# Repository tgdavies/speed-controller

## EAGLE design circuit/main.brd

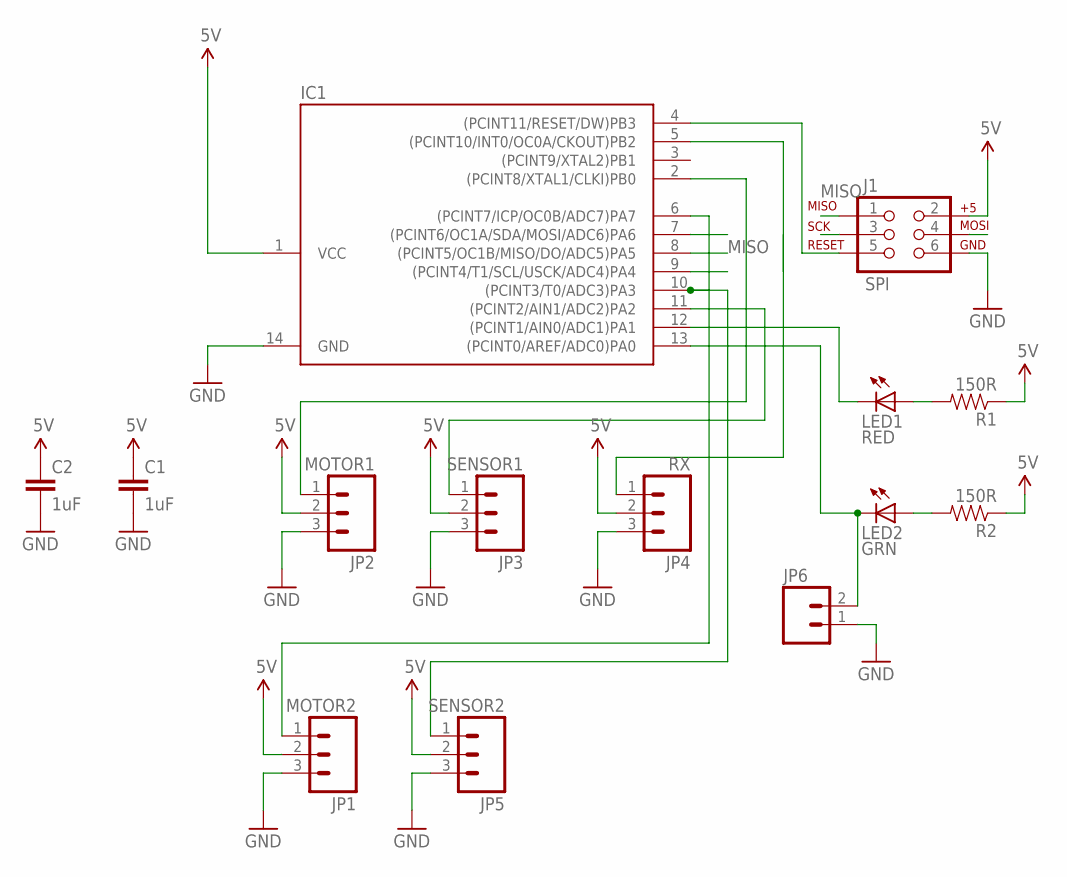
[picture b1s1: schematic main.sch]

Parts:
C1, C2: 1uF; 0805
IC1: ATTINY24/44/84-SSU; SOIC14
J1: SPI; 2X3_LOCK
JP1: MOTOR2; 1X03_LOCK
JP2: MOTOR1; 1X03_LOCK
JP3: SENSOR1; 1X03_LOCK
JP4: RX; 1X03_LOCK
JP5: SENSOR2; 1X03_LOCK
JP6: M02LOCK; 1X02_LOCK
LED1: RED; LED3MM
LED2: GRN; LED3MM
R1, R2: 150R; 0805

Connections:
5V: C1.1, C2.1, IC1.1 (VCC), J1.2, JP1.2, JP2.2, JP3.2, JP4.2, JP5.2, R1.1, R2.1
GND: C1.2, C2.2, IC1.14 (GND), J1.6, JP1.3, JP2.3, JP3.3, JP4.3, JP5.3, JP6.1
MISO: IC1.8 ((PCINT5/OC1B/MISO/DO/ADC5)PA5), J1.1
MOSI: IC1.7 ((PCINT6/OC1A/SDA/MOSI/ADC6)PA6), J1.4
unnamed: IC1.6 ((PCINT7/ICP/OC0B/ADC7)PA7), JP1.1
unnamed: IC1.5 ((PCINT10/INT0/OC0A/CKOUT)PB2), JP4.1
unnamed: IC1.10 ((PCINT3/T0/ADC3)PA3), JP5.1
unnamed: IC1.2 ((PCINT8/XTAL1/CLKI)PB0), JP2.1
unnamed: IC1.4 ((PCINT11/RESET/DW)PB3), J1.5
unnamed: IC1.12 ((PCINT1/AIN0/ADC1)PA1), LED1.K (C)
unnamed: LED1.A, R1.2
unnamed: IC1.13 ((PCINT0/AREF/ADC0)PA0), JP6.2, LED2.K (C)
unnamed: LED2.A, R2.2
unnamed: IC1.11 ((PCINT2/AIN1/ADC2)PA2), JP3.1
SCK: IC1.9 ((PCINT4/T1/SCL/USCK/ADC4)PA4), J1.3

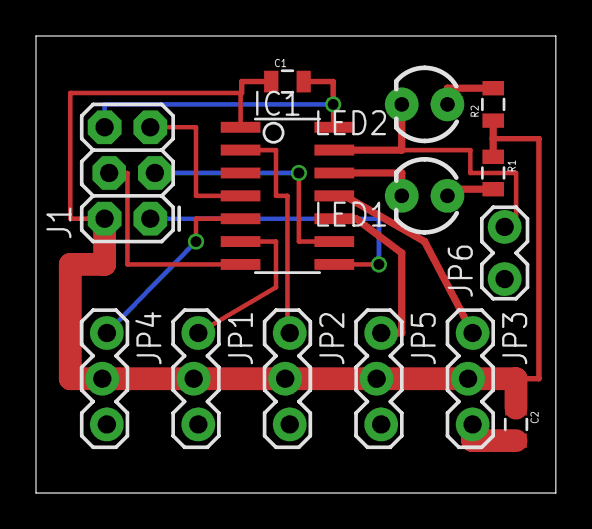
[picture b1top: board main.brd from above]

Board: 2 copper layers, 28.9 x 25.4 mm, 14 parts (0 on the bottom side), 15 nets.

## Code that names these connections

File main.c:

#include <avr/io.h>
#include <util/delay.h>
#include <avr/interrupt.h>
#include <stdint.h>
#include "avrutils.h"
#include "brushlesssensor.h"
#include "motor.h"
#include "pid.h"

#define RX_DD	(DDB2)
#define RX_P	(PB2) // Must be INT0 pin
#define MOTOR_DD (DDB0)
#define MOTOR2_DD (DDA7)
#define MOTOR_P (PB0)
#define MOTOR2_P (PA7)
#define SENSOR_DD (DDA2)
#define SENSOR2_DD (DDA3)
#define SENSOR_P (PA2)
#define SENSOR2_P (PA3) // does that work?
#define LED1_DD (DDA1)
#define LED1_P (PA1)
#define LED2_DD (DDA0)
#define LED2_P (PA0)

#define ISC0_RISE (0x03)
#define ISC0_FALL (0x02)

#define UART_SOFT_DDR DDRB 
#define UART_SOFT_PORT PORTB 
#define UART_SOFT_PIN PB1
#define UART_SOFT_BAUD (4800)

#define UART_SOFT_DELAY_US (int)(1000000.0/((float) UART_SOFT_BAUD)+0.5) 


#define softUartInit()   UART_SOFT_DDR |= (1<<UART_SOFT_PIN); \
                  UART_SOFT_PORT |= (1<<UART_SOFT_PIN)

#define DEBUG_CHARS_SIZE 9

#define readCNT1(X)         X = TCNT1L; \
        					X += TCNT1H << 8;

/*                  
char debugChars[DEBUG_CHARS_SIZE];
uint8_t sendDebug = 0;

void softUartSendChar(char txData) { 
     UART_SOFT_PORT &= ~(1<<UART_SOFT_PIN); 
     _delay_us(UART_SOFT_DELAY_US); 
   for (char i=0; i<8; i++) 
     { 
       if( txData & 1 ) 
            UART_SOFT_PORT |= (1<<UART_SOFT_PIN); 
       else 
            UART_SOFT_PORT &= ~(1<<UART_SOFT_PIN); 
       txData >>= 1; 
      _delay_us(UART_SOFT_DELAY_US); 
    } 
   UART_SOFT_PORT |= (1<<UART_SOFT_PIN); 
   _delay_us(UART_SOFT_DELAY_US); 
}

char hexDigit(int n) {
        if (n < 0xA) {
                return '0' + n;
        } else {
                return 'A' - 0xA + n;
        }
}

void clearDebugChars() {
        for (int i = 0; i < DEBUG_CHARS_SIZE; ++i) {
                debugChars[i] = 0;
        }
}

uint8_t debugIndex(uint8_t sizeNeeded) {
        uint8_t i = 0;
        while (i < DEBUG_CHARS_SIZE && debugChars[i] != 0)
                ++i;
        if (DEBUG_CHARS_SIZE - i >= sizeNeeded) {
                sendDebug = 1;
                return i;
        } else {
                return 0xff;
        }
}

void log8(uint8_t n) {
        uint8_t i = debugIndex(2);
        if (i != 0xff) {
                debugChars[i++] = hexDigit(n >> 4);
                debugChars[i] = hexDigit(n & 0x0F);
        }
}

void log16(uint16_t n) {
        uint8_t i = debugIndex(4);
        if (i != 0xff) {
                log8(n >> 8);
                log8(n & 0xFF);
        }
}

void logSep() {
        uint8_t i = debugIndex(1);
        if (i != 0xff) {
                debugChars[i] = ',';
        }
}

void logCRNL() {
        uint8_t i = debugIndex(2);
        if (i != 0xff) {
                debugChars[i++] = '\r';
                debugChars[i] = '\n';
        }
}


void softUartSendString (char *txData) 
{ 
   while(*txData != '\0') softUartSendChar(*txData++); 
}

void debugOn() {
    //PORTB |= (1 << PB4);
}

void debugOff() {
    //PORTB &= ~(1 << PB4);
}

void debugToggle() {
    //PORTB ^= (1 << PB4);
}*/


#define MAX_RPS INT16_C(50)

#define RX_COUNTS_PER_MS	125
#define RX_COUNT_STOP		62
#define RX_COUNT_DEAD_BAND	5

// controller input value after confining to 0..MAX_SPEED
volatile int16_t speed = 0;

// time to drive the motor in multiples of 4us
//volatile uint8_t drive = STOP_SPEED;

// really revs per second / 10
//volatile uint16_t actual_revs_per_second = 0;
volatile uint16_t desired_revs_per_second = 0;

#define AHEAD 1
#define ASTERN 2
volatile uint8_t desired_direction = 0;

#define BIT_DELAY_US(d,n) if (d & n) { _delay_us(n); }

void delay_us(uint16_t delay) {
    BIT_DELAY_US(delay, 0x200);
    BIT_DELAY_US(delay, 0x100);
    BIT_DELAY_US(delay, 0x80);
    BIT_DELAY_US(delay, 0x40);
    BIT_DELAY_US(delay, 0x20);
    BIT_DELAY_US(delay, 0x10);
    BIT_DELAY_US(delay, 0x08);
    BIT_DELAY_US(delay, 0x04);
    BIT_DELAY_US(delay, 0x02);
    BIT_DELAY_US(delay, 0x01);
}



//uint16_t debug_error = 0;
volatile uint16_t rx_signal_start_time = 0;
volatile uint16_t rx_signal_end_time = 0;

ISR(INT0_vect) {
    if (MCUCR != ISC0_RISE) {

        MCUCR = ISC0_RISE;
        rx_signal_end_time = TCNT1L;
        rx_signal_end_time += TCNT1H << 8;


        /*clearDebugChars();
        //log8(speed);
        //logSep();
        log8(desired_revs_per_second & 0xff);
        logSep();
        log16(actual_revs_per_second);
        //log8(v & 0xff);
        //logSep();
        //log8(error & 0xff);
        logCRNL();
                if (desired_revs_per_second == 0) {
                }*/
    } else {
        MCUCR = ISC0_FALL;
        rx_signal_start_time = TCNT1L;
        rx_signal_start_time += TCNT1H << 8;
        rx_signal_end_time = 0;
    }
}

void process_rx_result() {
    if (rx_signal_start_time != 0 && rx_signal_end_time != 0) {
        uint16_t v = timer_diff(rx_signal_start_time, rx_signal_end_time);
        if (v > RX_COUNTS_PER_MS * 3) { // invalid
            speed = RX_COUNT_STOP;
        } else if (v > RX_COUNTS_PER_MS * 2) {
            speed = RX_COUNTS_PER_MS;
        } else if (v < RX_COUNTS_PER_MS) {
            speed = 0;
        } else {
            speed = v - RX_COUNTS_PER_MS;
        }

        if (speed > RX_COUNT_STOP - RX_COUNT_DEAD_BAND && speed < RX_COUNT_STOP + RX_COUNT_DEAD_BAND) {
            speed = RX_COUNT_STOP;
            desired_revs_per_second = 0;
            desired_direction = 0;
            //debugOn();

        } else if (speed >= RX_COUNT_STOP + RX_COUNT_DEAD_BAND) {
            desired_revs_per_second = ((speed - (RX_COUNT_STOP + RX_COUNT_DEAD_BAND)) * MAX_RPS) / (RX_COUNTS_PER_MS - (RX_COUNT_STOP + RX_COUNT_DEAD_BAND));
            desired_direction = AHEAD;
        } else if (speed <= RX_COUNT_STOP - RX_COUNT_DEAD_BAND) {
            desired_revs_per_second = (((RX_COUNT_STOP - RX_COUNT_DEAD_BAND) - speed) * MAX_RPS) / (RX_COUNT_STOP - RX_COUNT_DEAD_BAND);
            desired_direction = ASTERN;
        }
        /*if (desired_direction && desired_revs_per_second < 10) {
                desired_revs_per_second = 10;
        }*/
        rx_signal_start_time = 0;
        rx_signal_end_time = 0;
    }
}



ESC all_escs[2];

SENSOR all_sensors[2];

PID all_pids[2];

uint8_t count = 0;

extern uint8_t rxBuf[];
extern uint8_t txBuf[];


/*	uint8_t pid_cycle_counter = 0;
        uint8_t previous_desired_direction = AHEAD;
    uint16_t previous_desired_revs_per_second = 0;
    int16_t integral = 0; */

/**
 * For the tiny84, PB2 (pin 5) is the RX input, PB0 (pin 2) is the servo output, and PA2 (pin 11, AIN1) is the sensor input
 * PB4 (pin 3) is the diagnostic LED output
 */
int main(void) {
    // set the clock prescaler to 1 to get us an 8MHz clock -- the CKDIV8 fuse is programmed by default, so initial prescaler is /8
    CLKPR = 0x80;
    CLKPR = 0x00;

    all_sensors[0].port = A;
    all_sensors[0].pin = PA2;
    all_sensors[1].port = A;
    all_sensors[1].pin = PA3;
    all_escs[0].port = B;
    all_escs[0].pin = PB0;
    all_escs[1].port = A;
    all_escs[1].pin = PA7;
    DDRA |= (1 << LED1_DD) | (1 << LED2_DD); // outputs for diagnostic LEDs and motor 2
    PORTA = 0x00;
    PORTB = 0x00;

    MCUCR = ISC0_RISE; // any change ISC0_RISE; // look for rising edge on INT0
    // enable interrupt INT0 for RX signal
    GIMSK |= (1 << INT0);
    TIMSK1 |= (1 << TOIE1) /*| (1 << OCIE1A) | (1 << OCIE1B)*/; // enable counter 1 overflow interrupt
    TCCR1B = 0x03; // CK/64, i.e. 125KHz (0.008ms), or 488Hz MSB or 1.9Hz overflow.
    red(1);
    green(0);
    setupEscs();
    usiTwiSlaveInit(0x10);
    sei();
    calibrateEscs();
    green(1);
    setupSensors();
    red(1);

    desired_direction = 0;
    desired_revs_per_second = 0;
    rxBuf[1] = 0;
    for (;;) {

        process_rx_result();
        if (rxBuf[0]) {
            desired_direction = (rxBuf[0] & 0x80) ? AHEAD : ASTERN;
            desired_revs_per_second = rxBuf[0] & 0x7f;
        }
        green(rxBuf[1]);
        processSensors();
        processPids();

        serviceEscs();
        txBuf[0] = desired_direction;
        txBuf[1] = desired_revs_per_second & 0xff;
        txBuf[2] = all_sensors[0].actual_revs_per_second & 0xff;
        txBuf[3] = all_escs[0].drive;
        txBuf[4] = all_sensors[1].actual_revs_per_second & 0xff;
        txBuf[5] = all_escs[1].drive;

        ++count;

    }
    return 0; /* never reached */
}

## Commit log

2012-06-16 Initial working version
2012-06-16 add dead spot in center of range
2012-06-17 change to use attinyx5 instead of at90s2312
2012-06-20 Initial RPM measurement working
2012-06-24 Use C99
2012-06-24 Add logging and PID
2012-06-28 serial debugging, attempt at PID using atmel application note
2012-07-15 change to a DIY PID -- with just 'I'
2012-07-29 initial attiny84 changes
2012-08-06 working in forwards direction with brushless and ESC
2012-08-07 handle invalid TX signals
2012-08-24 move code out of ISRs, add P term
2012-08-29 working ok, needs cleanup
2012-10-04 more tweaking, initial commit of morse code (ha ha)
2012-10-04 add eagle project
2012-11-27 Working fairly well with direct sensing
2012-12-03 Use pin change interrupts instead of analog comparator, to allow more sensors
2012-12-03 Only process ESC interrupt on a rising edge
2012-12-05 refactor ESC code
2012-12-06 sort ESCs by drive, add test
2012-12-06 use the new ESC code for the calibration too
2012-12-07 NON-WORKING: halfway thorugh generalising sensor
2012-12-08 beginning to work again after fixing stack overflow problems
2013-05-08 working with one motor and eagle tree preprocessor
2013-05-11 working with fixed rx buffer
2013-05-24 working version
2013-05-24 remove commented out code, reformat

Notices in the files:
parts and their libraries:
SparkFun: Licensing: CC v3.0 Share-Alike You are welcome to use this library for commercial purposes.
